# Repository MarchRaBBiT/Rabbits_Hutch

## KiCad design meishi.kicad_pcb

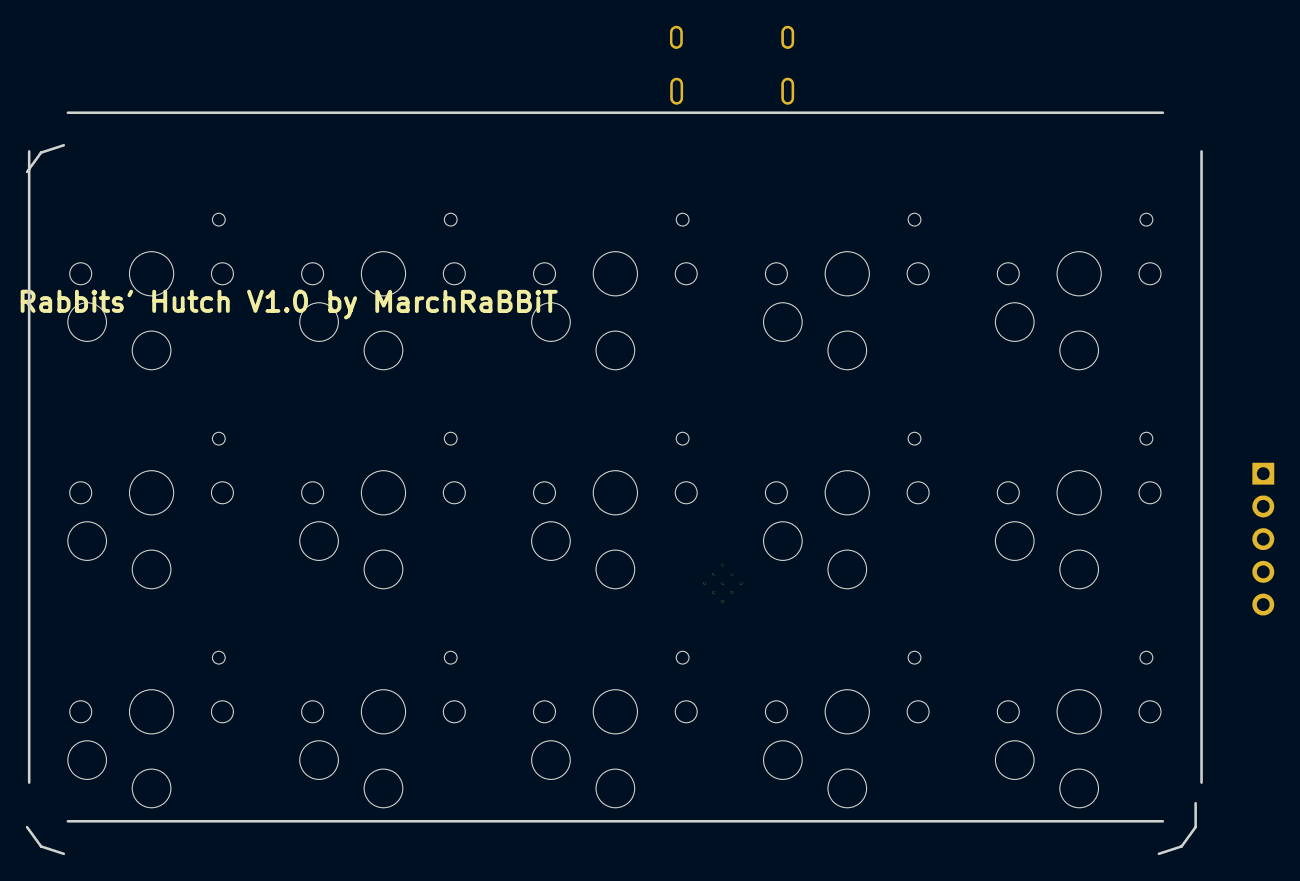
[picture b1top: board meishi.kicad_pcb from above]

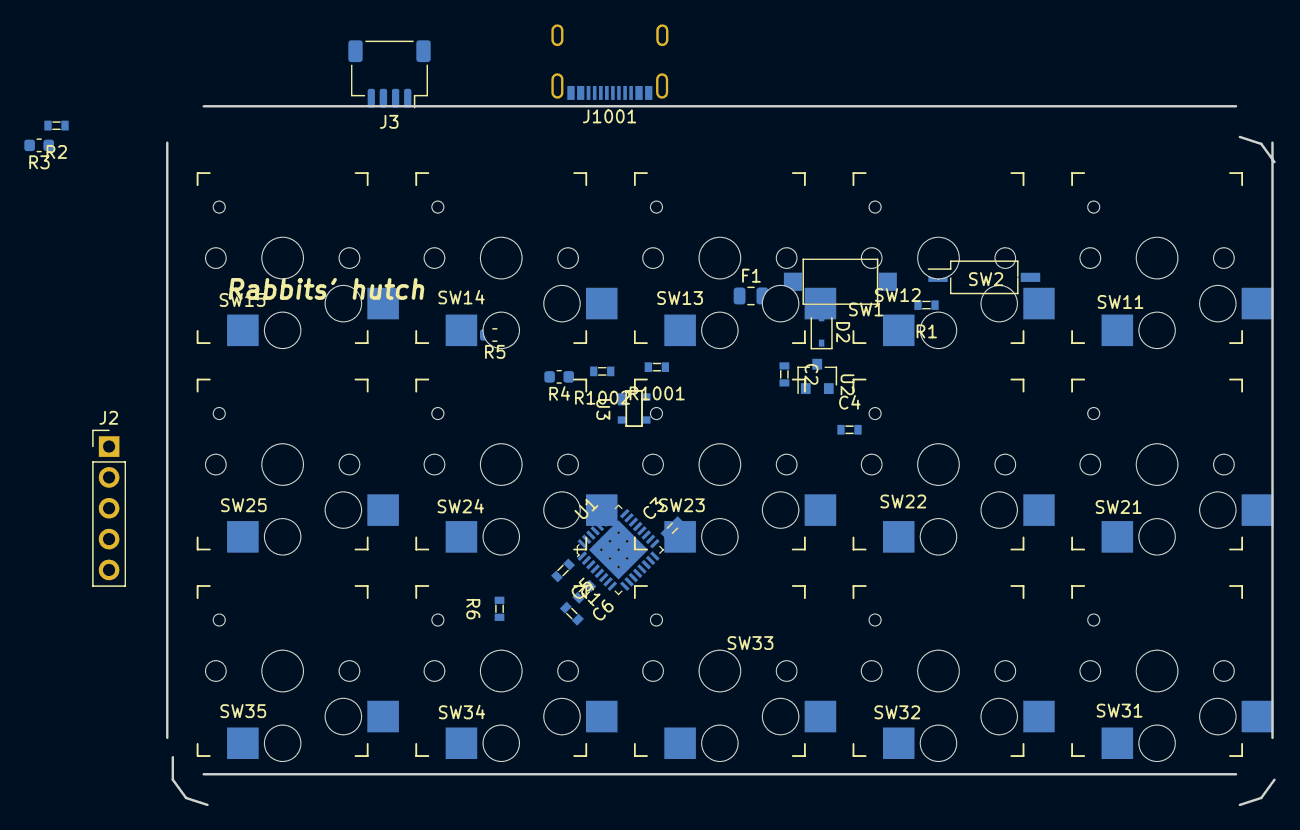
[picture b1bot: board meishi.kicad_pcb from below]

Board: 2 copper layers, 91.2 x 57.5 mm, 39 parts (24 on the bottom side), 30 nets, no tracks yet.

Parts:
C1, C3, C5, C6: 100n; 0603
C2, C4: 1u; 0603
D2: D_Schottky_Small; D_SOD-323
F1: Polyfuse_Small; Fuse_0805_2012Metric
J2: Conn_01x05; PinHeader_1x05_P2.54mm_Vertical
J3: Conn_01x04; JST_SH_SM04B-SRSS-TB_1x04-1MP_P1.00mm_Horizontal
J1001: E8124-015-01; SparkFun_15111
R1: 100k; 0603
R2: R_Small; 0603
R3: R_Small; R_0603_1608Metric
R4: 39k; R_0603_1608Metric
R5: 68k; R_0603_1608Metric
R6: 10k; 0603
R1001, R1002: 5.1k; 0603
SW1: SW_Push; SW_SPST_CK_RS282G05A3
SW2: SW_DIP_x01; SW_DIP_SPSTx01_Slide_Copal_CHS-01B_W7.62mm_P1.27mm
SW11, SW12, SW13, SW14, SW15, SW21, SW22, SW23, SW24, SW25, SW31, SW32, SW33, SW34, SW35: PG1350_Socket; PG1350_socket
U1: STM32F042K6U6; QFN-32-1EP_5x5mm
U2: MCP1703A-1202_SOT23; SOT-23
U3: PRTR5V0U2X; SOT143B

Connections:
BOOT0: R1.1, SW2.1, U1.32
D+: J1001.A6, J1001.B6, U1.22, U3.2
D-: J1001.A7, J1001.B7, U1.21, U3.3
GND: C1.2, C2.2, C3.2, C4.2, C5.2, C6.2, J2.3, J3.4, J1001.A1, J1001.B1, J1001.S1, R1.2, R5.2, R1001.2, R1002.1, SW1.2, SW11.2, SW12.2, SW13.2, SW14.2, SW15.2, SW21.2, SW22.2, SW23.2, SW24.2, SW25.2, SW31.2, SW32.2, SW33.2, SW34.2, SW35.2, U1.33, U2.1, U3.1
I2C1_SCL: J3.3, R3.2, U1.3
I2C1_SDA: J3.1, R2.1, U1.2
NRST: C1.1, J2.4, R6.2, SW1.1, U1.4
unnamed: C2.1, D2.1, U2.3
unnamed: J1001.A5, R1002.2
unnamed: J1001.B5, R1001.1
SW11: SW11.1, U1.28
SW12: SW12.1, U1.29
SW13: SW13.1, U1.30
SW14: SW14.1, U1.10
SW15: SW15.1, U1.11
SW21: SW21.1, U1.27
SW22: SW22.1, U1.8
SW23: SW23.1, U1.9
SW24: SW24.1, U1.12
SW25: SW25.1, U1.13
SW31: SW31.1, U1.26
SW32: SW32.1, U1.25
SW33: SW33.1, U1.20
SW34: SW34.1, U1.19
SW35: SW35.1, U1.18
SWDCLK: J2.2, U1.24
SWDIO: J2.5, U1.23
VBUS: D2.2, F1.1, F1.2, J1001.A4, J1001.B4, R4.1, U3.4
VBUS_Sense: R4.2, R5.1, U1.15
VDD: C3.1, C4.1, C5.1, C6.1, J2.1, J3.2, R2.2, R3.1, R6.1, SW2.2, U1.1, U1.5, U1.17, U2.2

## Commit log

2019-02-18 add dip switch for boot0
2019-02-18 fix physical collision of D1
2019-02-19 fix component layout
2019-02-19 add 3d data from qmk-hardware
2019-02-19 add rescue file
2019-03-10 fix unconnected SW22 to PA2 silk layer fix
2019-04-08 arrange silkscreen
2019-09-29 make changes
